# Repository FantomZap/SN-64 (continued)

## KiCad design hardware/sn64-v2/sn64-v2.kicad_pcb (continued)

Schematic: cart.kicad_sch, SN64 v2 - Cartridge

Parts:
C201, C202, C203, C204, C205, C206, C207, C208, C211, C213, C214, C215, C216, C217, C218, C219, C220: 100nF; C_0603_1608Metric; MPN CC0603KRX7R9BB104; LCSC C14663
C209, C210: 22uF 10V; C_0805_2012Metric; MPN CL21A226MAQNNNE; LCSC C45783
C212: 10uF 10V; C_0805_2012Metric; MPN CL21A106KAYNNNE; LCSC C15850
J1: N64 cartridge edge; N64_Edge_SC64_Reference
J2: SNES cartridge socket 62; SNES_Slot_Console_Straddle
R202, R203, R204, R209: 10k; R_0603_1608Metric; MPN 0603WAF1002T5E; LCSC C25804
R205, R206, R207, R208: 4.7k; R_0603_1608Metric; MPN 0603WAF4701T5E; LCSC C23162
R210, R211, R212, R213, R214: 100k; R_0603_1608Metric; MPN 0603WAF1003T5E; LCSC C25803
U201, U202, U203, U204: SN74ALVC164245DGGR; TSSOP-48_6.1x12.5mm_P0.5mm; MPN SN74ALVC164245DGGR; LCSC C7128
U205: SN74LVC07APWR; TSSOP-14_4.4x5mm_P0.65mm; MPN SN74LVC07APWR; LCSC C7809

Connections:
CIC_DATA0_OD: R202.2, U205.3; also elsewhere on the board
CIC_DATA1_OD: R203.2, U205.5; also elsewhere on the board
CIC_OE_N: R211.2, U203.25 (2~OE); also elsewhere on the board
CTL_OE_N: R210.2, U201.25 (2~OE), U201.48 (1~OE), U202.25 (2~OE), U202.48 (1~OE), U203.48 (1~OE); also elsewhere on the board
DATA_DIR: R213.2, U204.1 (1DIR); also elsewhere on the board
DATA_OE_N: R212.2, U204.48 (1~OE); also elsewhere on the board
FPGA_3V3: C201.1, C203.1, C205.1, C207.1, C211.1, C213.1, C215.1, C217.1, C219.1, R202.1, R203.1, R204.1, R210.1, R211.1, R212.1, R214.1, U201.1 (1DIR), U201.24 (2DIR), U201.31 (V_{CC(A)}), U201.42 (V_{CC(A)}), U202.1 (1DIR), U202.24 (2DIR), U202.31 (V_{CC(A)}), U202.42 (V_{CC(A)}), U203.1 (1DIR), U203.24 (2DIR), U203.31 (V_{CC(A)}), U203.42 (V_{CC(A)}), U204.31 (V_{CC(A)}), U204.42 (V_{CC(A)}), U205.14 (VCC); also elsewhere on the board
GND: C201.2, C202.2, C203.2, C204.2, C205.2, C206.2, C207.2, C208.2, C209.2, C210.2, C211.2, C212.2, C213.2, C214.2, C215.2, C216.2, C217.2, C218.2, C219.2, C220.2, J1.1 (GND), J1.2 (GND), J1.6 (GND), J1.22 (GND), J1.23 (GND), J1.25 (GND), J1.26 (GND), J1.27 (GND), J1.31 (GND), J1.47 (GND), J1.48 (GND), J1.50 (GND), J2.5 (GND), J2.36 (GND), R213.1, U201.4 (GND), U201.10 (GND), U201.15 (GND), U201.21 (GND), U201.28 (GND), U201.34 (GND), U201.39 (GND), U201.45 (GND), U202.4 (GND), U202.10 (GND), U202.15 (GND), U202.21 (GND), U202.28 (GND), U202.34 (GND), U202.39 (GND), U202.45 (GND), U203.4 (GND), U203.10 (GND), U203.15 (GND), U203.21 (GND), U203.26 (2A7), U203.27 (2A6), U203.28 (GND), U203.29 (2A5), U203.30 (2A4), U203.32 (2A3), U203.34 (GND), U203.39 (GND), U203.45 (GND), U204.4 (GND), U204.10 (GND), U204.15 (GND), U204.19 (2B4), U204.20 (2B5), U204.21 (GND), U204.22 (2B6), U204.23 (2B7), U204.24 (2DIR), U204.26 (2A7), U204.27 (2A6), U204.28 (GND), U204.29 (2A5), U204.30 (2A4), U204.34 (GND), U204.39 (GND), U204.45 (GND), U205.1, U205.7 (GND), U205.11, U205.13; also elsewhere on the board
HOST_3V3: C212.1, J1.9 (3V3), J1.17 (3V3), J1.34 (3V3), J1.42 (3V3); also elsewhere on the board
L_A0: U201.47 (1A0); also elsewhere on the board
L_A1: U201.46 (1A1); also elsewhere on the board
L_A2: U201.44 (1A2); also elsewhere on the board
L_A3: U201.43 (1A3); also elsewhere on the board
L_A4: U201.41 (1A4); also elsewhere on the board
L_A5: U201.40 (1A5); also elsewhere on the board
L_A6: U201.38 (1A6); also elsewhere on the board
L_A7: U201.37 (1A7); also elsewhere on the board
L_A8: U201.36 (2A0); also elsewhere on the board
L_A9: U201.35 (2A1); also elsewhere on the board
L_A10: U201.33 (2A2); also elsewhere on the board
L_A11: U201.32 (2A3); also elsewhere on the board
L_A12: U201.30 (2A4); also elsewhere on the board
L_A13: U201.29 (2A5); also elsewhere on the board
L_A14: U201.27 (2A6); also elsewhere on the board
L_A15: U201.26 (2A7); also elsewhere on the board
L_A16: U202.47 (1A0); also elsewhere on the board
L_A17: U202.46 (1A1); also elsewhere on the board
L_A18: U202.44 (1A2); also elsewhere on the board
L_A19: U202.43 (1A3); also elsewhere on the board
L_A20: U202.41 (1A4); also elsewhere on the board
L_A21: U202.40 (1A5); also elsewhere on the board
L_A22: U202.38 (1A6); also elsewhere on the board
L_A23: U202.37 (1A7); also elsewhere on the board
L_CIC_CLK: U203.35 (2A1); also elsewhere on the board
L_CIC_DATA0_IN: U204.36 (2A0); also elsewhere on the board
L_CIC_DATA1_IN: U204.35 (2A1); also elsewhere on the board
L_CIC_SLAVE_RESET: U203.33 (2A2); also elsewhere on the board
L_D0: U204.47 (1A0); also elsewhere on the board
L_D1: U204.46 (1A1); also elsewhere on the board
L_D2: U204.44 (1A2); also elsewhere on the board
L_D3: U204.43 (1A3); also elsewhere on the board
L_D4: U204.41 (1A4); also elsewhere on the board
L_D5: U204.40 (1A5); also elsewhere on the board
L_D6: U204.38 (1A6); also elsewhere on the board
L_D7: U204.37 (1A7); also elsewhere on the board
L_IRQ_N: U204.33 (2A2); also elsewhere on the board
L_PA0: U203.47 (1A0); also elsewhere on the board
L_PA1: U203.46 (1A1); also elsewhere on the board
L_PA2: U203.44 (1A2); also elsewhere on the board
L_PA3: U203.43 (1A3); also elsewhere on the board
L_PA4: U203.41 (1A4); also elsewhere on the board
L_PA5: U203.40 (1A5); also elsewhere on the board
L_PA6: U203.38 (1A6); also elsewhere on the board
L_PA7: U203.37 (1A7); also elsewhere on the board
L_PHI2: U202.26 (2A7); also elsewhere on the board
L_PRD_N: U202.33 (2A2); also elsewhere on the board
L_PWR_N: U202.32 (2A3); also elsewhere on the board
L_RD_N: U202.36 (2A0); also elsewhere on the board
L_REFRESH: U202.27 (2A6); also elsewhere on the board
L_RESET_N_SENSE: U204.32 (2A3); also elsewhere on the board
L_ROMSEL_N: U202.30 (2A4); also elsewhere on the board
L_SYSTEM_CLK: U203.36 (2A0); also elsewhere on the board
L_WRAMSEL_N: U202.29 (2A5); also elsewhere on the board
L_WR_N: U202.35 (2A1); also elsewhere on the board
N64_AD0: J1.28 (AD0); also elsewhere on the board
N64_AD1: J1.29 (AD1); also elsewhere on the board
N64_AD2: J1.30 (AD2); also elsewhere on the board
N64_AD3: J1.32 (AD3); also elsewhere on the board
N64_AD4: J1.36 (AD4); also elsewhere on the board
N64_AD5: J1.37 (AD5); also elsewhere on the board
N64_AD6: J1.40 (AD6); also elsewhere on the board
N64_AD7: J1.41 (AD7); also elsewhere on the board
N64_AD8: J1.16 (AD8); also elsewhere on the board
N64_AD9: J1.15 (AD9); also elsewhere on the board
N64_AD10: J1.12 (AD10); also elsewhere on the board
N64_AD11: J1.11 (AD11); also elsewhere on the board
N64_AD12: J1.7 (AD12); also elsewhere on the board
N64_AD13: J1.5 (AD13); also elsewhere on the board
N64_AD14: J1.4 (AD14); also elsewhere on the board
N64_AD15: J1.3 (AD15); also elsewhere on the board
N64_ALE_H: J1.35 (ALE_H); also elsewhere on the board
N64_ALE_L: J1.33 (ALE_L); also elsewhere on the board
N64_CIC_CLK: J1.43 (CIC_CLK); also elsewhere on the board
N64_CIC_DATA: J1.18 (CIC_DATA); also elsewhere on the board
N64_INT_N: J1.44 (/INT); also elsewhere on the board
N64_JOYBUS: J1.21 (JOYBUS); also elsewhere on the board
N64_NMI_N: J1.45 (/NMI); also elsewhere on the board
N64_PIF_CLK: J1.19 (PIF_CLK); also elsewhere on the board
N64_READ_N: J1.10 (/READ); also elsewhere on the board
N64_RESET_N: J1.20 (/RESET); also elsewhere on the board
N64_WRITE_N: J1.8 (/WRITE); also elsewhere on the board
RESET_PULL_OD: R204.2, U205.9; also elsewhere on the board
SENSE_OE_N: R214.2, U204.25 (2~OE); also elsewhere on the board
SNES_5V_CART: C202.1, C204.1, C206.1, C208.1, C209.1, C210.1, C214.1, C216.1, C218.1, C220.1, J2.27 (+5V_CART), J2.58 (+5V_CART), R205.1, R206.1, R207.1, R208.1, R209.1, U201.7 (V_{CC(B)}), U201.18 (V_{CC(B)}), U202.7 (V_{CC(B)}), U202.18 (V_{CC(B)}), U203.7 (V_{CC(B)}), U203.18 (V_{CC(B)}), U204.7 (V_{CC(B)}), U204.18 (V_{CC(B)}); also elsewhere on the board
SNES_A0: J2.17 (A0), U201.2 (1B0)
SNES_A1: J2.16 (A1), U201.3 (1B1)
SNES_A2: J2.15 (A2), U201.5 (1B2)
SNES_A3: J2.14 (A3), U201.6 (1B3)
SNES_A4: J2.13 (A4), U201.8 (1B4)
SNES_A5: J2.12 (A5), U201.9 (1B5)
SNES_A6: J2.11 (A6), U201.11 (1B6)
SNES_A7: J2.10 (A7), U201.12 (1B7)
SNES_A8: J2.9 (A8), U201.13 (2B0)
SNES_A9: J2.8 (A9), U201.14 (2B1)
SNES_A10: J2.7 (A10), U201.16 (2B2)
SNES_A11: J2.6 (A11), U201.17 (2B3)
SNES_A12: J2.37 (A12), U201.19 (2B4)
SNES_A13: J2.38 (A13), U201.20 (2B5)
SNES_A14: J2.39 (A14), U201.22 (2B6)
SNES_A15: J2.40 (A15), U201.23 (2B7)
SNES_A16: J2.41 (A16), U202.2 (1B0)
SNES_A17: J2.42 (A17), U202.3 (1B1)
SNES_A18: J2.43 (A18), U202.5 (1B2)
SNES_A19: J2.44 (A19), U202.6 (1B3)
SNES_A20: J2.45 (A20), U202.8 (1B4)
SNES_A21: J2.46 (A21), U202.9 (1B5)
SNES_A22: J2.47 (A22), U202.11 (1B6)
SNES_A23: J2.48 (A23), U202.12 (1B7)
SNES_AUDIO_L_IN: J2.31 (AUDIO_L_IN); also elsewhere on the board
SNES_AUDIO_R_IN: J2.62 (AUDIO_R_IN); also elsewhere on the board
SNES_CIC_CLK: J2.56 (CIC_CLK), U203.14 (2B1)
SNES_CIC_DATA0: J2.55 (CIC_DATA0), R205.2, U204.13 (2B0), U205.4
SNES_CIC_DATA1: J2.24 (CIC_DATA1), R206.2, U204.14 (2B1), U205.6
SNES_CIC_SLAVE_RESET: J2.25 (CIC_SLAVE_RESET), U203.16 (2B2)
SNES_D0: J2.19 (D0), U204.2 (1B0)
SNES_D1: J2.20 (D1), U204.3 (1B1)
SNES_D2: J2.21 (D2), U204.5 (1B2)
SNES_D3: J2.22 (D3), U204.6 (1B3)
SNES_D4: J2.50 (D4), U204.8 (1B4)
SNES_D5: J2.51 (D5), U204.9 (1B5)
SNES_D6: J2.52 (D6), U204.11 (1B6)
SNES_D7: J2.53 (D7), U204.12 (1B7)
SNES_EXPAND: J2.2 (EXPAND), R209.2
SNES_IRQ_N: J2.18 (/IRQ), R208.2, U204.16 (2B2)
SNES_PA0: J2.28 (PA0), U203.2 (1B0)
SNES_PA1: J2.59 (PA1), U203.3 (1B1)
SNES_PA2: J2.29 (PA2), U203.5 (1B2)
SNES_PA3: J2.60 (PA3), U203.6 (1B3)
SNES_PA4: J2.30 (PA4), U203.8 (1B4)
SNES_PA5: J2.61 (PA5), U203.9 (1B5)
SNES_PA6: J2.3 (PA6), U203.11 (1B6)
SNES_PA7: J2.34 (PA7), U203.12 (1B7)
SNES_PHI2: J2.57 (PHI2), U202.23 (2B7)
SNES_PRD_N: J2.4 (/PRD), U202.16 (2B2)
SNES_PWR_N: J2.35 (/PWR), U202.17 (2B3)
SNES_RD_N: J2.23 (/RD), U202.13 (2B0)
SNES_REFRESH: J2.33 (REFRESH), U202.22 (2B6)
SNES_RESET_N: J2.26 (/RESET), R207.2, U204.17 (2B3), U205.8
SNES_ROMSEL_N: J2.49 (/ROMSEL), U202.19 (2B4)
SNES_SYSTEM_CLK: J2.1 (SYSTEM_CLK), U203.13 (2B0)
SNES_WRAMSEL_N: J2.32 (/WRAMSEL), U202.20 (2B5)
SNES_WR_N: J2.54 (/WR), U202.14 (2B1)

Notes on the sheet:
SN64 v2 CARTRIDGE SHEET - N64 edge J1 and SNES socket J2 on the one board, four SN74ALVC164245 translators (A = 3.3 V, B = 5 V), SN74LVC07A open-drain driver for the 5 V lines the FPGA pulls.

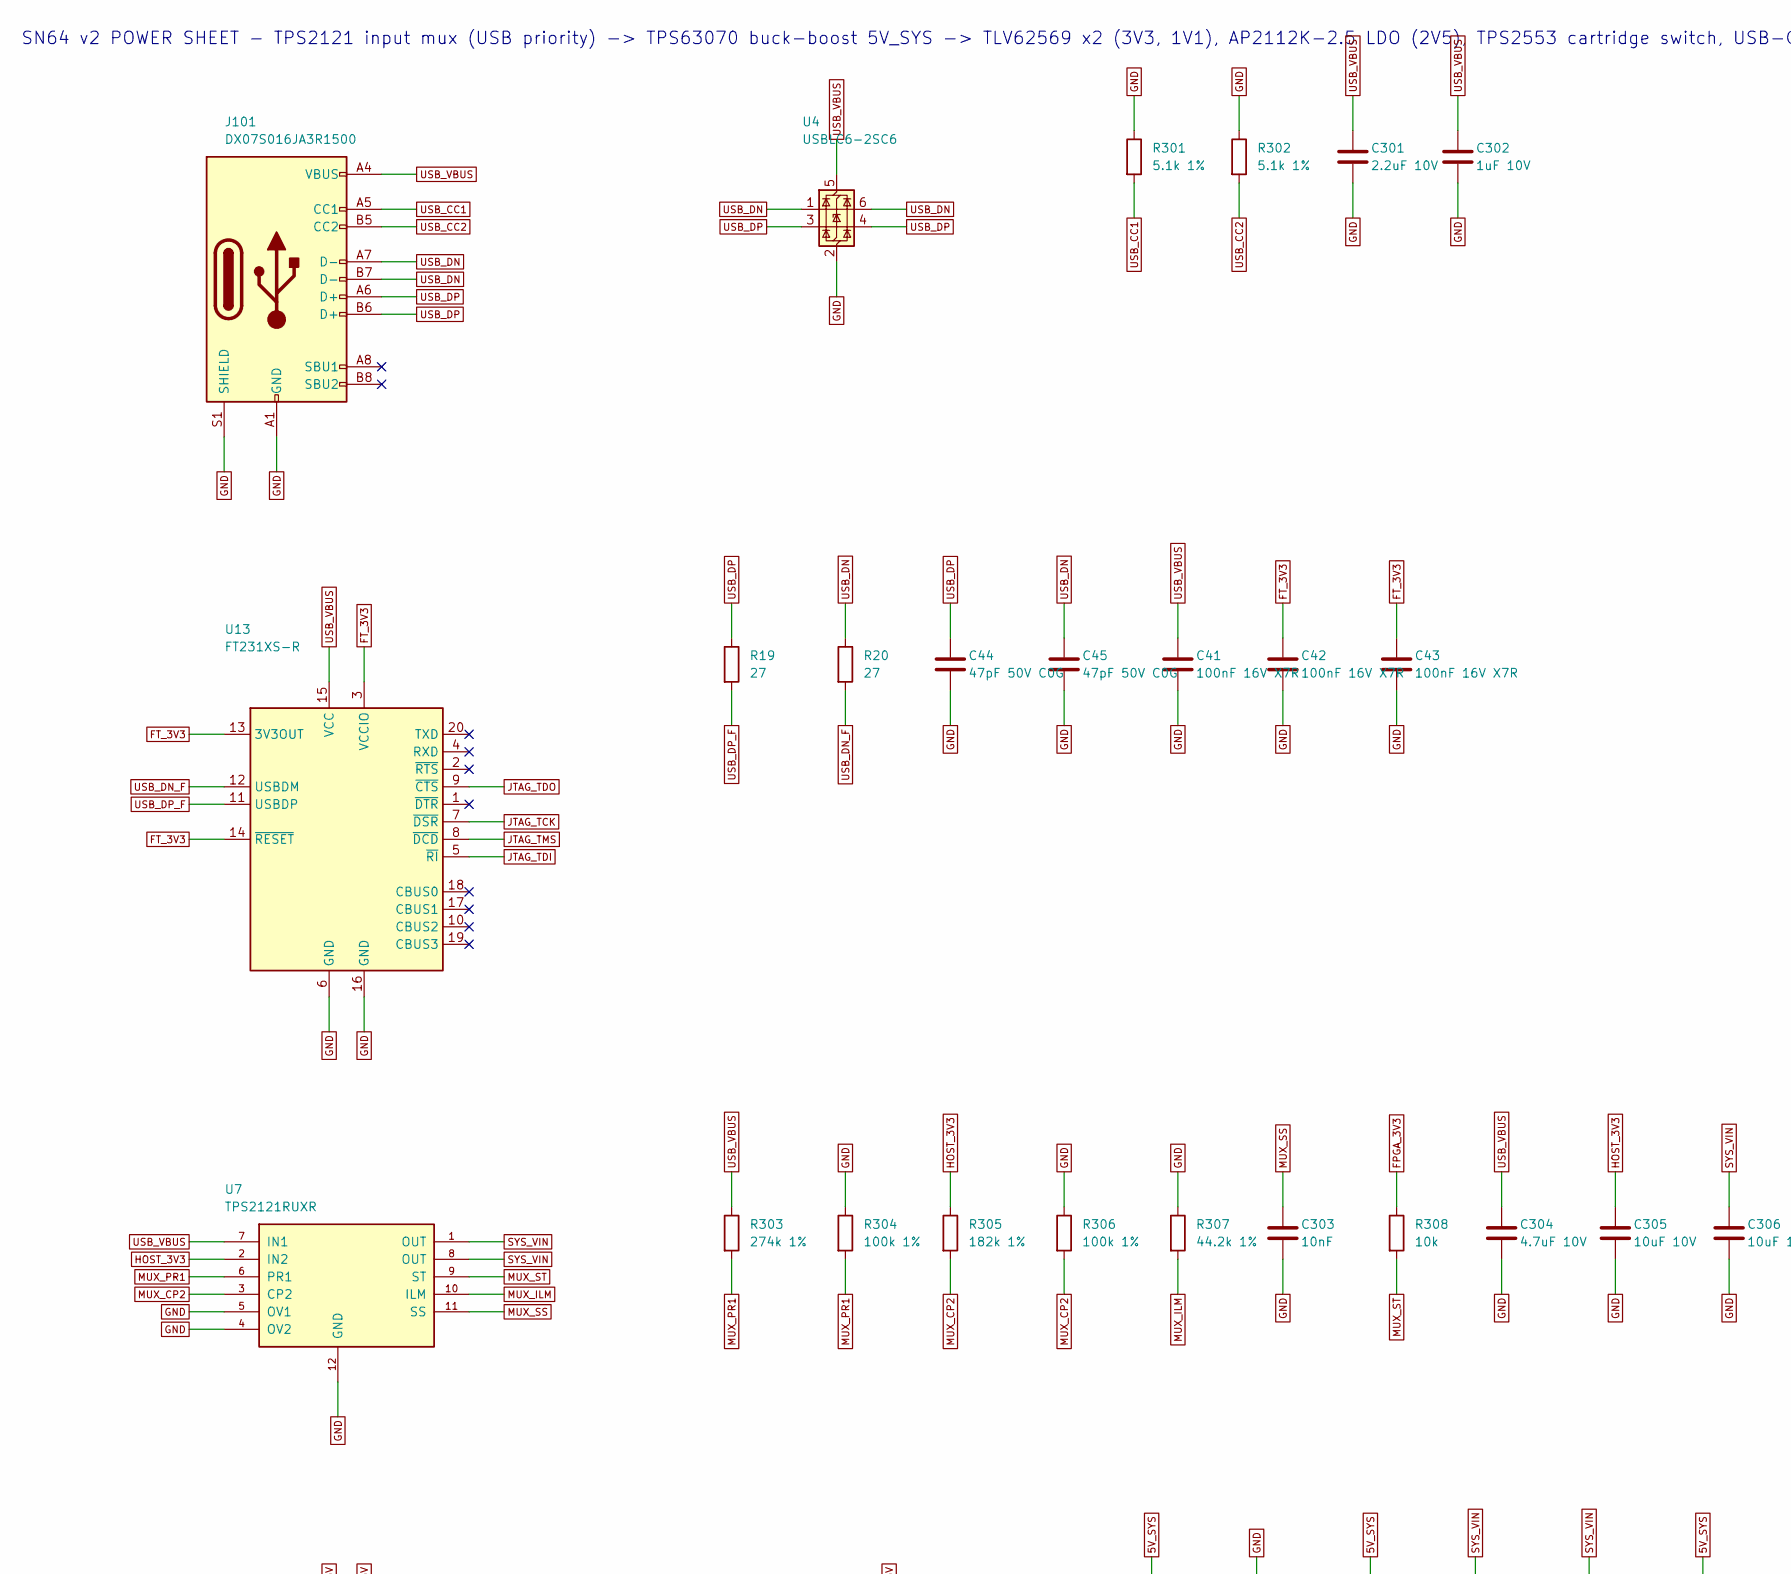
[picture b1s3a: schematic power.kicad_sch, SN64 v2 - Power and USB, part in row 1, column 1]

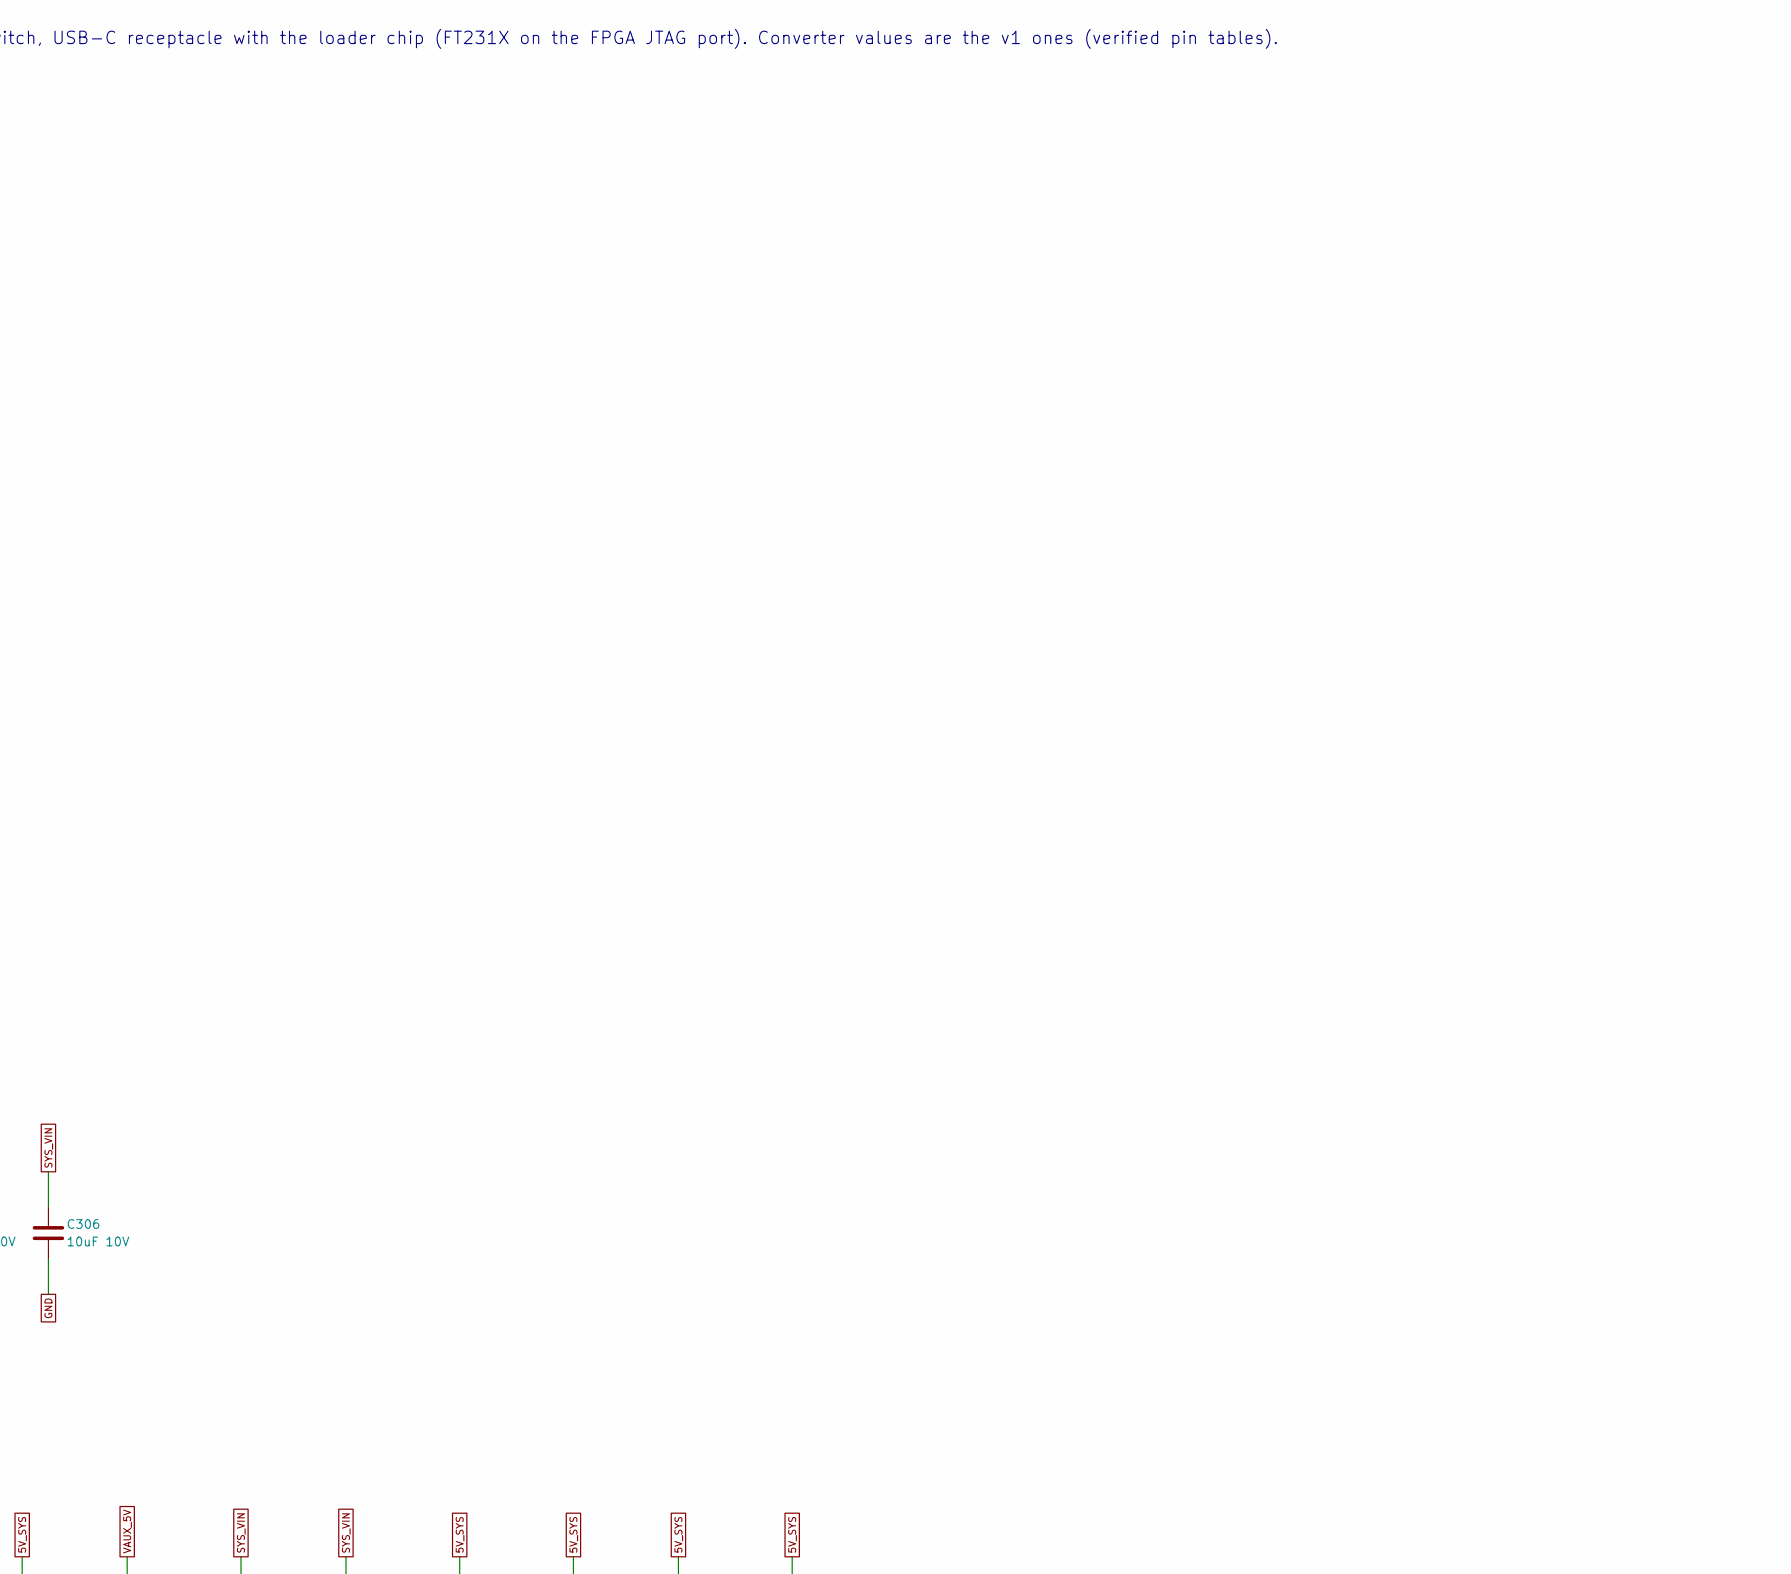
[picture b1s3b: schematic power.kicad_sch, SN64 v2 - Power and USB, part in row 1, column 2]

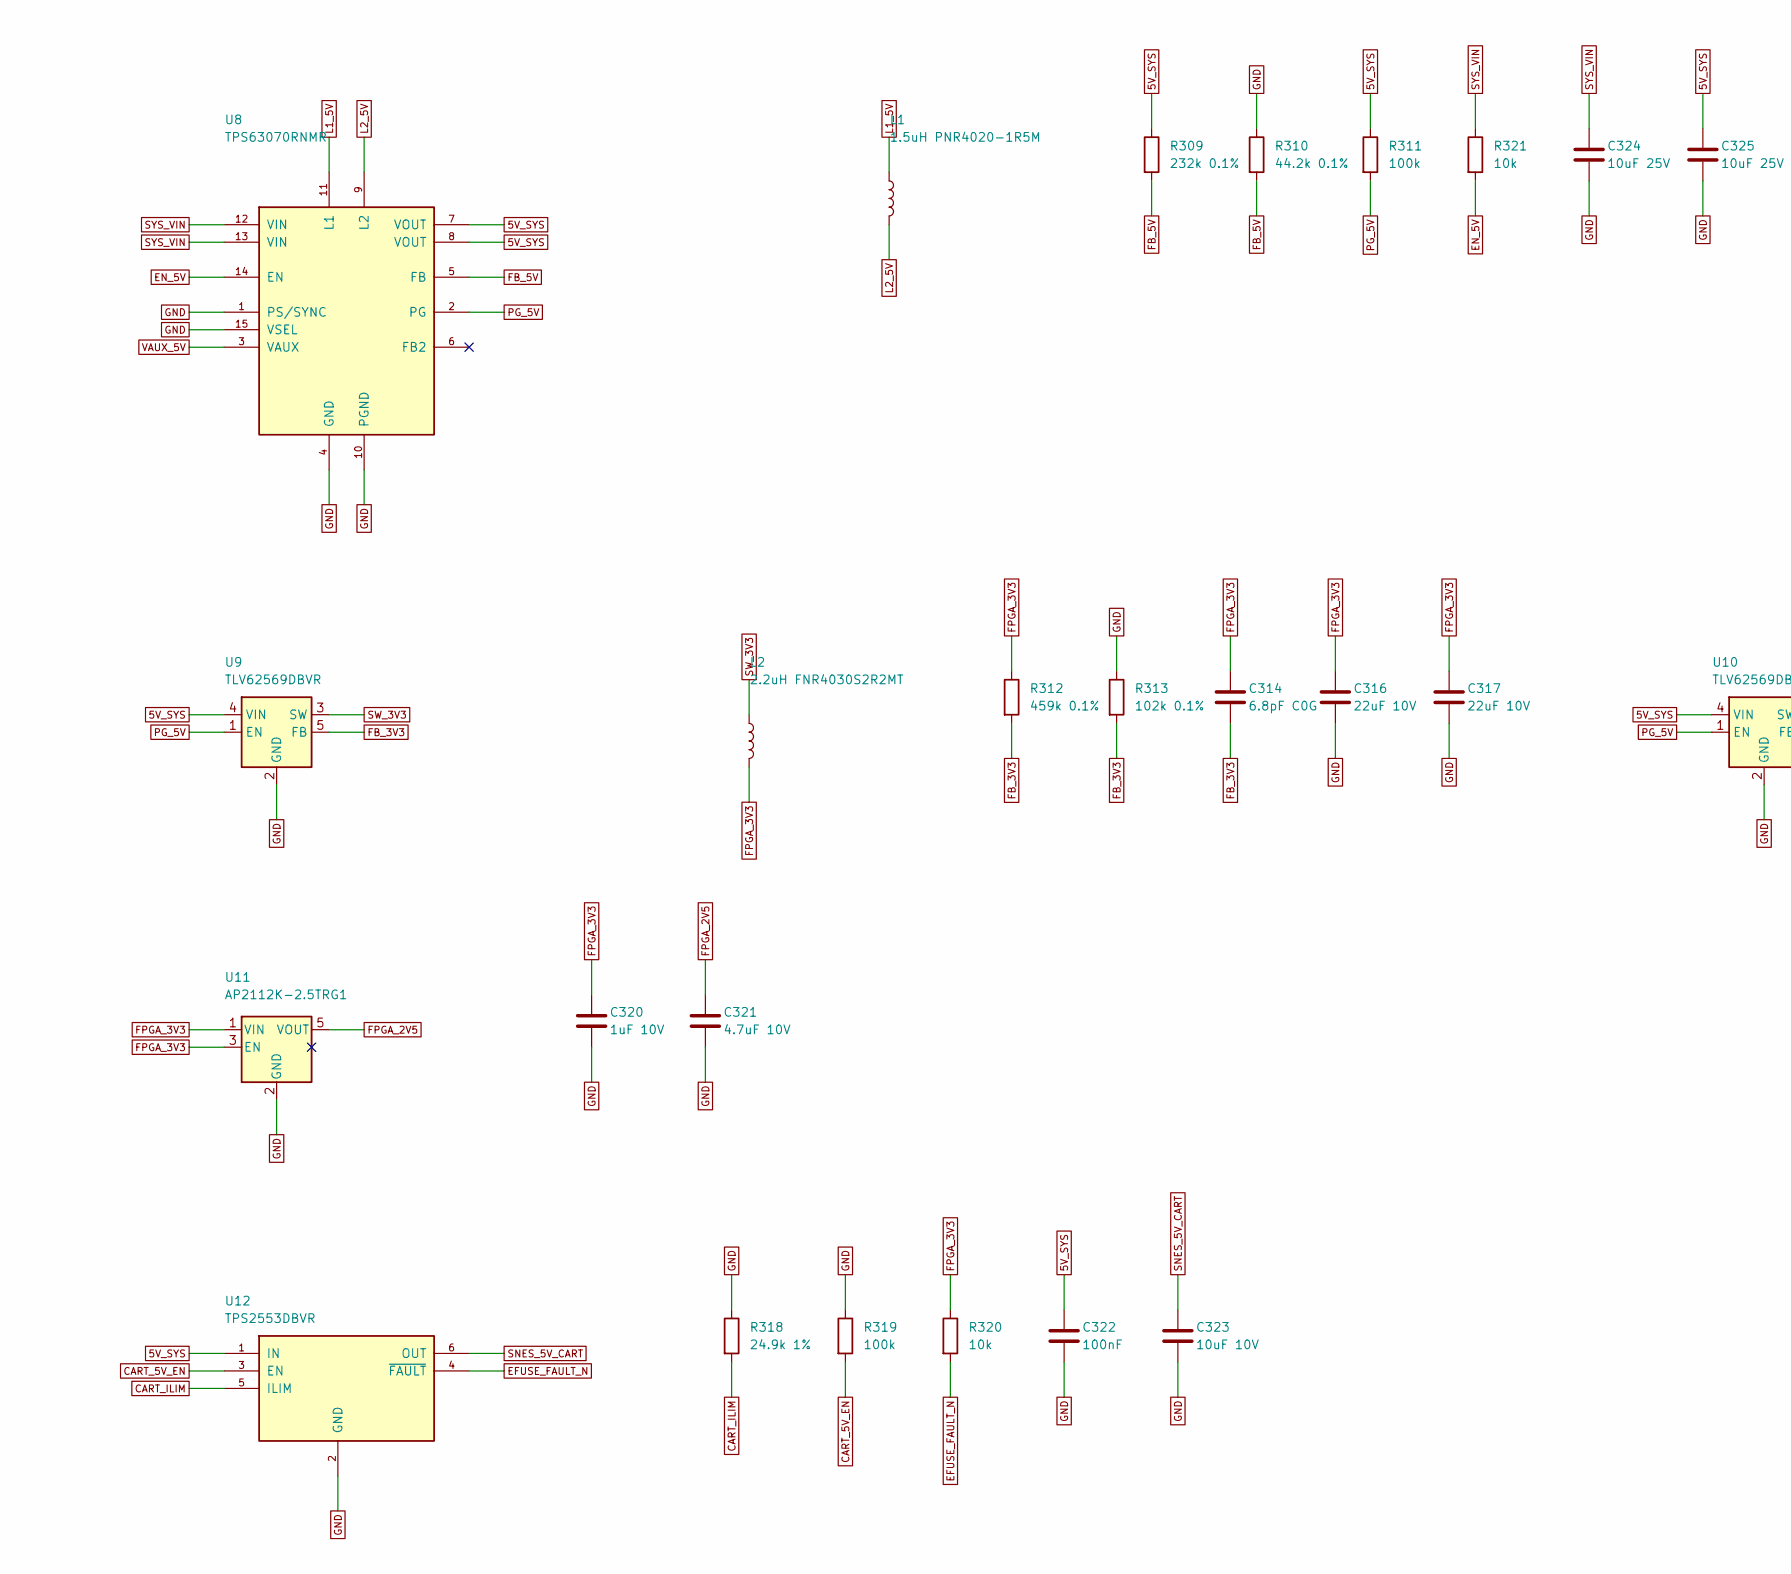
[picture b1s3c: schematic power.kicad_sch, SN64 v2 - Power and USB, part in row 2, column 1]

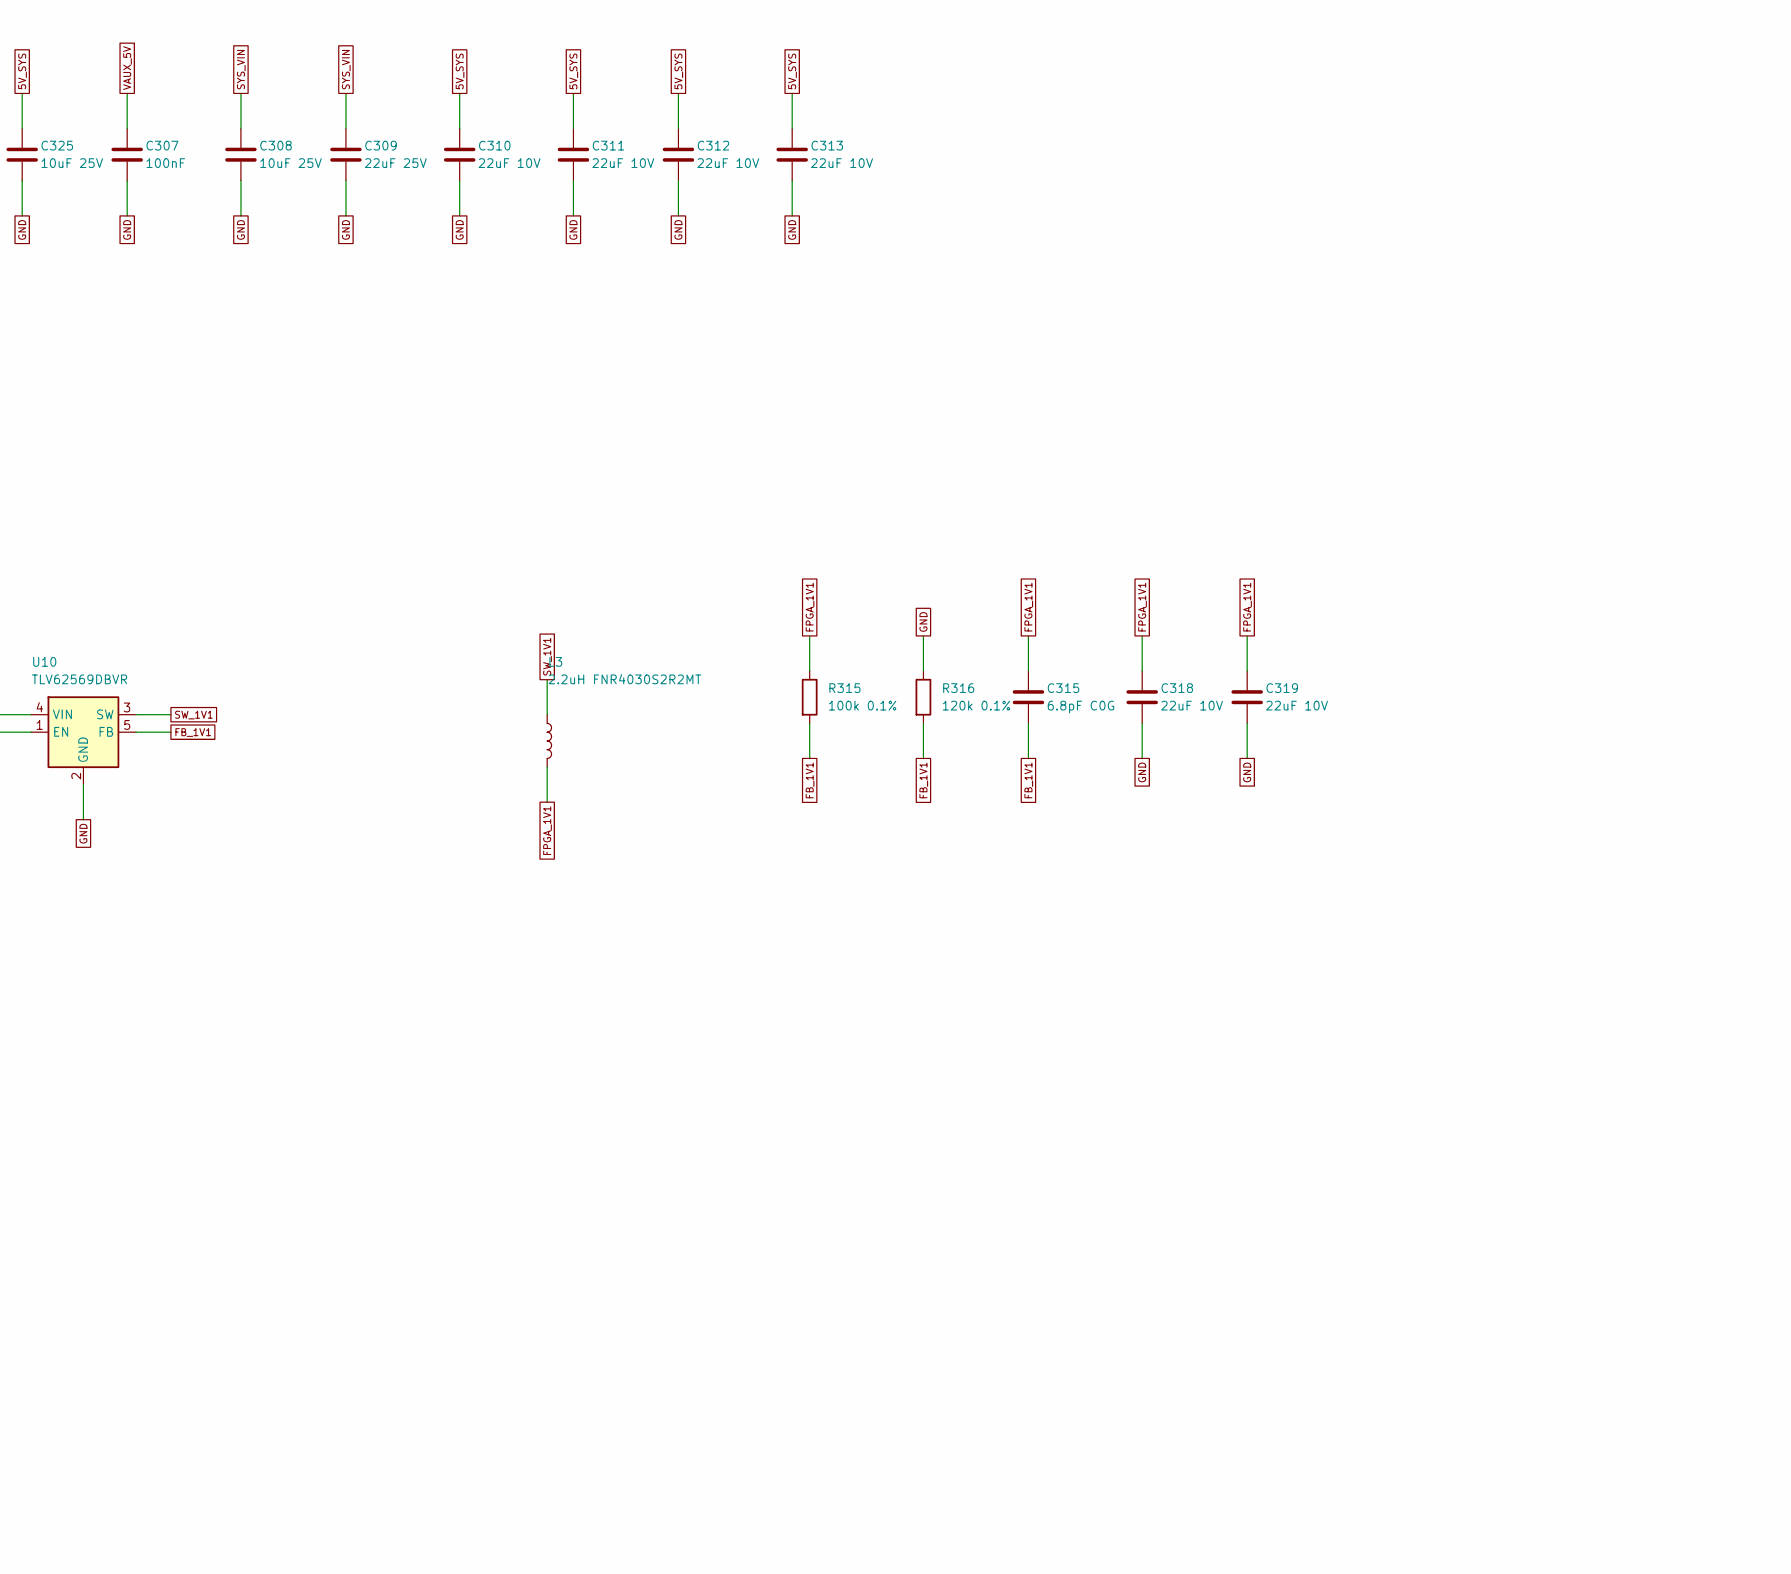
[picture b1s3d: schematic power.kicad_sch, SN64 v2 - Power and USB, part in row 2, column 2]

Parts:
C41, C42, C43: 100nF 16V X7R; C_0603_1608Metric; MPN CC0603KRX7R9BB104; LCSC C14663
C44, C45: 47pF 50V C0G; C_0603_1608Metric; MPN CL10C470JB8NNNC; LCSC C1671
C301: 2.2uF 10V; C_0805_2012Metric; MPN CL21A225KBQNNNE; LCSC C377773
C302, C320: 1uF 10V; C_0603_1608Metric; MPN CL10A105KB8NNNC; LCSC C15849
C303: 10nF; C_0603_1608Metric; MPN 0603B103K500NT; LCSC C57112
C304, C321: 4.7uF 10V; C_0805_2012Metric; MPN CL21A475KAQNNNE; LCSC C1779
C305, C306, C323: 10uF 10V; C_0805_2012Metric; MPN CL21A106KAYNNNE; LCSC C15850
C307, C322: 100nF; C_0603_1608Metric; MPN CC0603KRX7R9BB104; LCSC C14663
C308: 10uF 25V; C_0805_2012Metric; MPN CL21A106KAYNNNE; LCSC C15850
C309: 22uF 25V; C_0805_2012Metric; MPN CL21A226MAQNNNE; LCSC C45783
C310, C311, C312, C313, C316, C317, C318, C319: 22uF 10V; C_0805_2012Metric; MPN CL21A226MAQNNNE; LCSC C45783
C314, C315: 6.8pF C0G; C_0603_1608Metric; MPN 0603CG6R8C500NT; LCSC C1679
C324, C325: 10uF 25V; C_0603_1608Metric; MPN CL10A106MA8NRNC; LCSC C96446
J101: DX07S016JA3R1500; USB_C_JAE_DX07S016JA3R1500; MPN DX07S016JA3R1500; LCSC C2939926
L1: 1.5uH PNR4020-1R5M; L_APV_PNR4020; MPN PNR4020-1R5M; LCSC C54620133
L2, L3: 2.2uH FNR4030S2R2MT; L_Changjiang_FNR4030S; MPN FNR4030S2R2MT; LCSC C167869
R19, R20: 27; R_0603_1608Metric; MPN 0603WAF270JT5E; LCSC C25190
R301, R302: 5.1k 1%; R_0603_1608Metric; MPN 0603WAF5101T5E; LCSC C23186
R303: 274k 1%; R_0603_1608Metric; MPN FRC0603F2743TS; LCSC C5126128
R304, R306: 100k 1%; R_0603_1608Metric; MPN 0603WAF1003T5E; LCSC C25803
R305: 182k 1%; R_0603_1608Metric; MPN FRC0603F1823TS; LCSC C5126102
R307: 44.2k 1%; R_0603_1608Metric; MPN FRC0603F4422TS; LCSC C2930103
R308, R320, R321: 10k; R_0603_1608Metric; MPN 0603WAF1002T5E; LCSC C25804
R309: 232k 0.1%; R_0603_1608Metric; MPN RT0603BRD07232KL; LCSC C861240
R310: 44.2k 0.1%; R_0603_1608Metric; MPN RT0603BRD0744K2L; LCSC C861410
R311, R319: 100k; R_0603_1608Metric; MPN 0603WAF1003T5E; LCSC C25803
R312: 459k 0.1%; R_0603_1608Metric; MPN RT0603BRD07459KL; LCSC C6288321
R313: 102k 0.1%; R_0603_1608Metric; MPN RT0603BRD07102KL; LCSC C861068
R315: 100k 0.1%; R_0603_1608Metric; MPN RT0603BRD07100KL; LCSC C122538
R316: 120k 0.1%; R_0603_1608Metric; MPN RT0603BRD07120KL; LCSC C705720
R318: 24.9k 1%; R_0603_1608Metric; MPN 0603WAF2492T5E; LCSC C25962
U4: USBLC6-2SC6; SOT-23-6; MPN USBLC6-2SC6; LCSC C7519
U7: TPS2121RUXR; Texas_VQFN-HR-12_2x2.5mm_P0.5mm; MPN TPS2121RUXR; LCSC C485916
U8: TPS63070RNMR; Texas_RNM0015A_VQFN-HR-15_2.5x3mm; MPN TPS63070RNMR; LCSC C109322
U9, U10: TLV62569DBVR; SOT-23-5; MPN TLV62569DBVR; LCSC C141836
U11: AP2112K-2.5TRG1; SOT-23-5; MPN AP2112K-2.5TRG1; LCSC C51118
U12: TPS2553DBVR; SOT-23-6; MPN TPS2553DBVR; LCSC C55266
U13: FT231XS-R; SSOP-20_3.9x8.7mm_P0.635mm; MPN FT231XS-R; LCSC C132160

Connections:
5V_SYS: C310.1, C311.1, C312.1, C313.1, C322.1, C325.1, R309.1, R311.1, U8.7 (VOUT), U8.8 (VOUT), U9.4 (VIN), U10.4 (VIN), U12.1 (IN); also elsewhere on the board
CART_5V_EN: R319.2, U12.3 (EN); also elsewhere on the board
CART_ILIM: R318.2, U12.5 (ILIM)
EFUSE_FAULT_N: R320.2, U12.4 (~FAULT); also elsewhere on the board
EN_5V: R321.2, U8.14 (EN)
FB_1V1: C315.2, R315.2, R316.2, U10.5 (FB)
FB_3V3: C314.2, R312.2, R313.2, U9.5 (FB)
FB_5V: R309.2, R310.2, U8.5 (FB)
FPGA_1V1: C315.1, C318.1, C319.1, L3.2, R315.1; also elsewhere on the board
FPGA_2V5: C321.1, U11.5 (VOUT); also elsewhere on the board
FPGA_3V3: C314.1, C316.1, C317.1, C320.1, L2.2, R308.1, R312.1, R320.1, U11.1 (VIN), U11.3 (EN); also elsewhere on the board
FT_3V3: C42.1, C43.1, U13.3 (VCCIO), U13.13 (3V3OUT), U13.14 (~RESET)
GND: C41.2, C42.2, C43.2, C44.2, C45.2, C301.2, C302.2, C303.2, C304.2, C305.2, C306.2, C307.2, C308.2, C309.2, C310.2, C311.2, C312.2, C313.2, C316.2, C317.2, C318.2, C319.2, C320.2, C321.2, C322.2, C323.2, C324.2, C325.2, J101.A1 (GND), J101.A12 (GND), J101.B1 (GND), J101.B12 (GND), J101.S1 (SHIELD), R301.1, R302.1, R304.1, R306.1, R307.1, R310.1, R313.1, R316.1, R318.1, R319.1, U4.2 (GND), U7.4 (OV2), U7.5 (OV1), U7.12 (GND), U8.1 (PS/SYNC), U8.4 (GND), U8.10 (PGND), U8.15 (VSEL), U9.2 (GND), U10.2 (GND), U11.2 (GND), U12.2 (GND), U13.6 (GND), U13.16 (GND); also elsewhere on the board
HOST_3V3: C305.1, R305.1, U7.2 (IN2); also elsewhere on the board
JTAG_TCK: U13.7 (~DSR); also elsewhere on the board
JTAG_TDI: U13.5 (~RI); also elsewhere on the board
JTAG_TDO: U13.9 (~CTS); also elsewhere on the board
JTAG_TMS: U13.8 (~DCD); also elsewhere on the board
L1_5V: L1.1, U8.11 (L1)
L2_5V: L1.2, U8.9 (L2)
MUX_CP2: R305.2, R306.2, U7.3 (CP2)
MUX_ILM: R307.2, U7.10 (ILM)
MUX_PR1: R303.2, R304.2, U7.6 (PR1)
MUX_SS: C303.1, U7.11 (SS)
MUX_ST: R308.2, U7.9 (ST); also elsewhere on the board
PG_5V: R311.2, U8.2 (PG), U9.1 (EN), U10.1 (EN)
SNES_5V_CART: C323.1, U12.6 (OUT); also elsewhere on the board
SW_1V1: L3.1, U10.3 (SW)
SW_3V3: L2.1, U9.3 (SW)
SYS_VIN: C306.1, C308.1, C309.1, C324.1, R321.1, U7.1 (OUT), U7.8 (OUT), U8.12 (VIN), U8.13 (VIN)
USB_CC1: J101.A5 (CC1), R301.2; also elsewhere on the board
USB_CC2: J101.B5 (CC2), R302.2; also elsewhere on the board
USB_DN: C45.1, J101.A7 (D-), J101.B7 (D-), R20.1, U4.1 (I/O1), U4.6 (I/O1)
USB_DN_F: R20.2, U13.12 (USBDM)
USB_DP: C44.1, J101.A6 (D+), J101.B6 (D+), R19.1, U4.3 (I/O2), U4.4 (I/O2)
USB_DP_F: R19.2, U13.11 (USBDP)
USB_VBUS: C41.1, C301.1, C302.1, C304.1, J101.A4 (VBUS), J101.A9 (VBUS), J101.B4 (VBUS), J101.B9 (VBUS), R303.1, U4.5 (VBUS), U7.7 (IN1), U13.15 (VCC); also elsewhere on the board
VAUX_5V: C307.1, U8.3 (VAUX)

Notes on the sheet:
SN64 v2 POWER SHEET - TPS2121 input mux (USB priority) -> TPS63070 buck-boost 5V_SYS -> TLV62569 x2 (3V3, 1V1), AP2112K-2.5 LDO (2V5), TPS2553 cartridge switch, USB-C receptacle with the loader chip (FT231X on the FPGA JTAG port). Converter values are the v1 ones (verified pin tables).
